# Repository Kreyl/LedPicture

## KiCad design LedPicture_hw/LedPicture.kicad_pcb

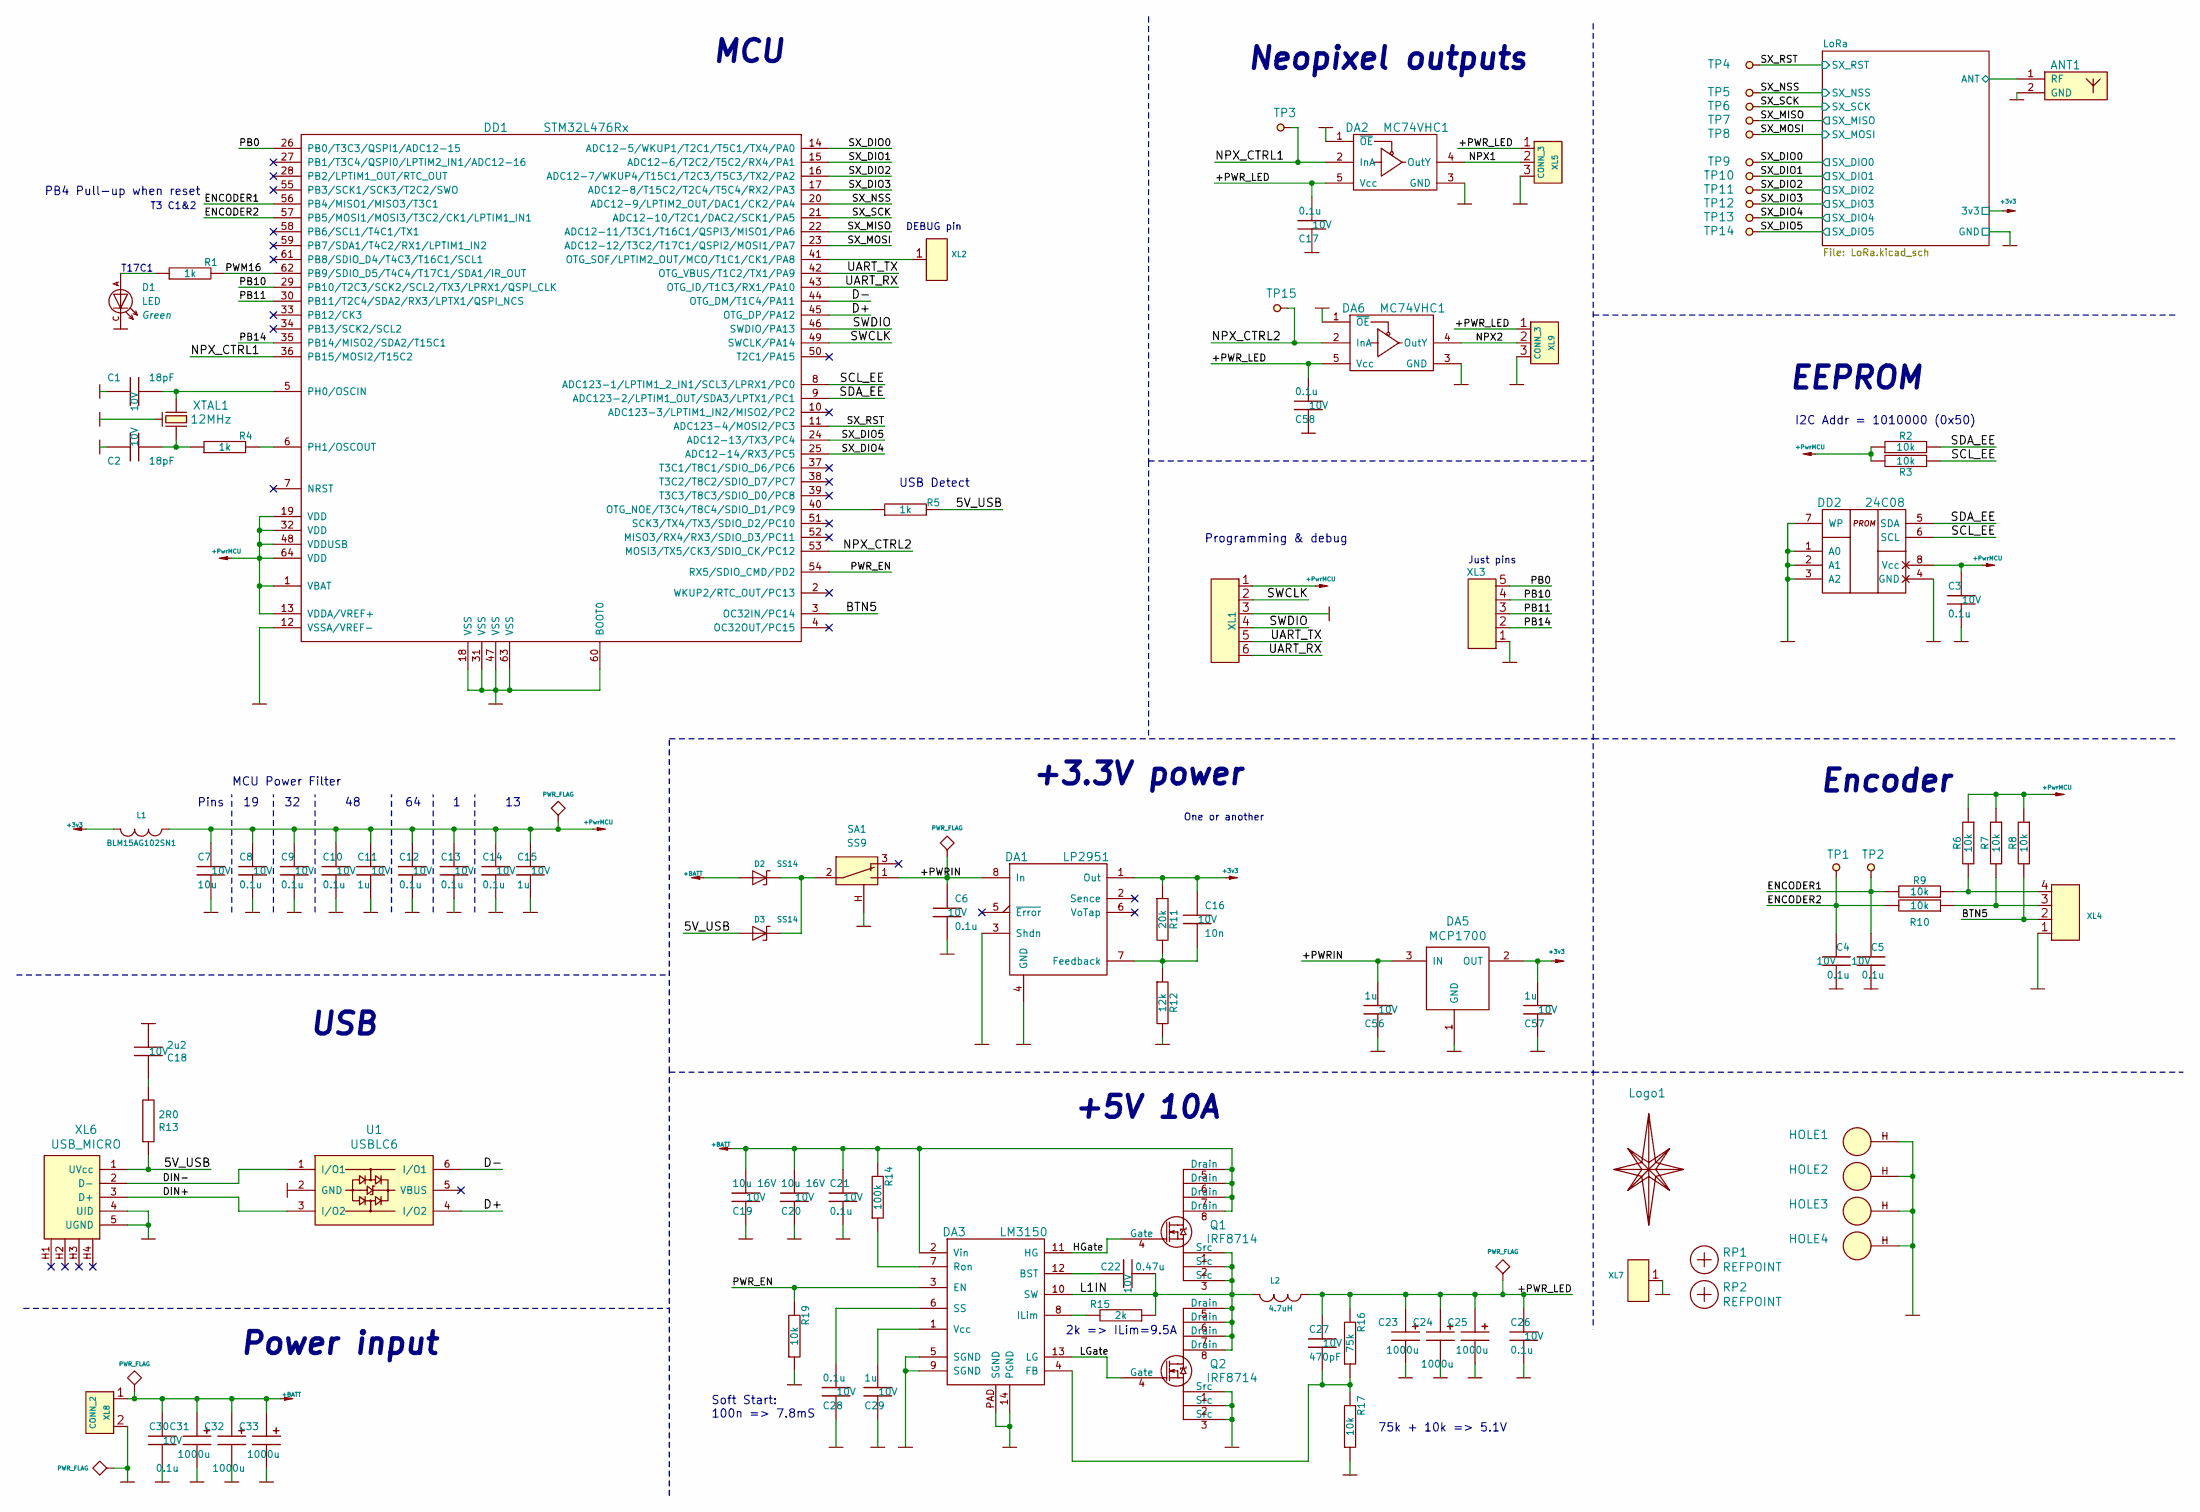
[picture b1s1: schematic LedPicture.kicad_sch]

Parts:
ANT1: ANT_GENERAL; ANT_868_IFA_SIMPLEJOY
C1, C2: 18pF; CAP_0603_Silks; Tolerance 20%; Voltage 10V
C3, C4, C5, C6, C8, C9, C10, C12, C13, C14, C17, C21, C26, C28, C30, C58: 0.1u; CAP_0603_Silks; Tolerance 20%; Voltage 10V
C7: 10u; CAP_0603_Silks; Tolerance 20%; Voltage 10V
C11, C15, C29, C56, C57: 1u; CAP_0603_Silks; Tolerance 20%; Voltage 10V
C16: 10n; CAP_0603_Silks; Tolerance 20%; Voltage 10V
C18: 2u2; CAP_0603_Silks; Tolerance 20%; Voltage 10V
C19, C20: 10u 16V; CAP_0603_Silks; Tolerance 20%; Voltage 10V
C22: 0.47u; CAP_0603_Silks; Tolerance 20%; Voltage 10V
C23, C24, C25, C31, C32, C33: 1000u; CAP_10xxR
C27: 470pF; CAP_0603_Silks; Tolerance 20%; Voltage 10V
D1: LED; LED_0603
D2, D3: SS14; SMA_DO214AC
DA1: LP2951; SO8_150MIL
DA2, DA6: MC74VHC1; SOT23-5
DA3: LM3150; HTSSOP14
DA5: MCP1700; SOT23-3A
DD1: STM32L476Rx; LQFP64
DD2: 24C08; SO8_150MIL
HOLE1, HOLE2, HOLE3, HOLE4: HOLE_METALLED; Hole3_5_out6mm
L1: BLM15AG102SN1; IND_0402; Tolerance 20%
L2: 4.7uH; 13x13
Logo1: Logo; Ostranna_16d9_13d5
Q1, Q2: IRF8714; SO8_150MIL
R1, R4, R5: 1k; RES_0603; Tolerance 1%
R2, R3, R6, R7, R8, R9, R10, R17, R19: 10k; RES_0603; Tolerance 1%
R11: 20k; RES_0603; Tolerance 1%
R12: 12k; RES_0603; Tolerance 1%
R13: 2R0; RES_0603; Tolerance 1%
R14: 100k; RES_0603; Tolerance 1%
R15: 2k; RES_0603; Tolerance 1%
R16: 75k; RES_0603; Tolerance 1%
RP1, RP2: REFPOINT; REF_POINT_1MM
SA1: SS9; SW_SS9
TP1, TP2, TP3, TP4, TP5, TP6, TP7, TP8, TP9, TP10, TP11, TP12, TP13, TP14, TP15: TESTPOINT; TESTPOINT_1MM
U1: USBLC6; SOT23-6
XL1: CONN_6; PLS-6_LOCK
XL2, XL7: CONN_1; PLS-1Rnd
XL3: CONN_5; PLS-5
XL4: CONN_4; WB-04(MW-4M)
XL5, XL9: CONN_3; TermiBlockHeader_508_x3_R
XL6: USB_MICRO; USBmicro_MOLEX_1050170001
XL8: CONN_2; TermiBlockHeader_508_x2_R
XTAL1: 12MHz; 03225C4

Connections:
+3v3: C16.1, C57.1, DA1.1 (Out), DA5.2 (OUT), L1.2, R11.1; also elsewhere on the board
+BATT: C19.1, C20.1, C21.2, C30.2, C31.1, C32.1, C33.1, D2.A, DA3.2 (Vin), Q1.5 (Drain), Q1.6 (Drain), Q1.7 (Drain), Q1.8 (Drain), R14.2, XL8.1
/5V_USB: D3.A, R5.2, R13.1, XL6.1 (UVcc)
/+PWRIN: C6.1, C56.1, DA1.8 (In), DA5.3 (IN), SA1.1
/+PWR_LED: C17.1, C23.1, C24.1, C25.1, C26.2, C27.2, C58.1, DA2.5 (Vcc), DA6.5 (Vcc), L2.1, R16.2, XL5.1, XL9.1
/BTN5: DD1.3 (OC32IN/PC14), R8.2, XL4.2 (PM)
/D+: DD1.45 (OTG_DP/PA12), U1.4 (I/O2)
/D-: DD1.44 (OTG_DM/T1C4/PA11), U1.6 (I/O1)
/DIN+: U1.3 (I/O2), XL6.3 (D+)
/DIN-: U1.1 (I/O1), XL6.2 (D-)
/ENCODER1: C5.2, DD1.56 (PB4/MISO1/MISO3/T3C1), R9.2, TP2.1
/ENCODER2: C4.2, DD1.57 (PB5/MOSI1/MOSI3/T3C2/CK1/LPTIM1_IN1), R10.2, TP1.1
/HGate: DA3.11 (HG), Q1.4 (Gate)
/L1IN: C22.1, DA3.10 (SW), L2.2, Q1.1 (Src), Q1.2 (Src), Q1.3 (Src), Q2.5 (Drain), Q2.6 (Drain), Q2.7 (Drain), Q2.8 (Drain), R15.1
/LGate: DA3.13 (LG), Q2.4 (Gate)
/LoRa/ANT: ANT1.1 (RF); also elsewhere on the board
/NPX1: DA2.4 (OutY), XL5.2 (PM)
/NPX2: DA6.4 (OutY), XL9.2 (PM)
/NPX_CTRL1: DA2.2 (InA), DD1.36 (PB15/MOSI2/T15C2), TP3.1
/NPX_CTRL2: DA6.2 (InA), DD1.53 (MOSI3/TX5/CK3/SDIO_CK/PC12), TP15.1
/PB0: DD1.26 (PB0/T3C3/QSPI1/ADC12-15), XL3.5
/PB10: DD1.29 (PB10/T2C3/SCK2/SCL2/TX3/LPRX1/QSPI_CLK), XL3.4
/PB11: DD1.30 (PB11/T2C4/SDA2/RX3/LPTX1/QSPI_NCS), XL3.3
/PB14: DD1.35 (PB14/MISO2/SDA2/T15C1), XL3.2
/PWM16: DD1.62 (PB9/SDIO_D5/T4C4/T17C1/SDA1/IR_OUT), R1.2
/PWR_EN: DA3.3 (EN), DD1.54 (RX5/SDIO_CMD/PD2), R19.2
/SCL_EE: DD1.8 (ADC123-1/LPTIM1_2_IN1/SCL3/LPRX1/PC0), DD2.6 (SCL), R3.1
/SDA_EE: DD1.9 (ADC123-2/LPTIM1_OUT/SDA3/LPTX1/PC1), DD2.5 (SDA), R2.2
/SWCLK: DD1.49 (SWCLK/PA14), XL1.2
/SWDIO: DD1.46 (SWDIO/PA13), XL1.4
/SX_DIO0: DD1.14 (ADC12-5/WKUP1/T2C1/T5C1/TX4/PA0), TP9.1; also elsewhere on the board
/SX_DIO1: DD1.15 (ADC12-6/T2C2/T5C2/RX4/PA1), TP10.1; also elsewhere on the board
/SX_DIO2: DD1.16 (ADC12-7/WKUP4/T15C1/T2C3/T5C3/TX2/PA2), TP11.1; also elsewhere on the board
/SX_DIO3: DD1.17 (ADC12-8/T15C2/T2C4/T5C4/RX2/PA3), TP12.1; also elsewhere on the board
/SX_DIO4: DD1.25 (ADC12-14/RX3/PC5), TP13.1; also elsewhere on the board
/SX_DIO5: DD1.24 (ADC12-13/TX3/PC4), TP14.1; also elsewhere on the board
/SX_MISO: DD1.22 (ADC12-11/T3C1/T16C1/QSPI3/MISO1/PA6), TP7.1; also elsewhere on the board
/SX_MOSI: DD1.23 (ADC12-12/T3C2/T17C1/QSPI2/MOSI1/PA7), TP8.1; also elsewhere on the board
/SX_NSS: DD1.20 (ADC12-9/LPTIM2_OUT/DAC1/CK2/PA4), TP5.1; also elsewhere on the board
/SX_RST: DD1.11 (ADC123-4/MOSI2/PC3), TP4.1; also elsewhere on the board
/SX_SCK: DD1.21 (ADC12-10/T2C1/DAC2/SCK1/PA5), TP6.1; also elsewhere on the board
/UART_RX: DD1.43 (OTG_ID/T1C3/RX1/PA10), XL1.6
/UART_TX: DD1.42 (OTG_VBUS/T1C2/TX1/PA9), XL1.5
GND: ANT1.2 (GND), C1.2, C2.2, C3.1, C4.1, C5.1, C6.2, C7.1, C8.1, C9.1, C10.1, C11.1, C12.1, C13.1, C14.1, C15.1, C17.2, C18.2, C19.2, C20.2, C21.1, C23.2, C24.2, C25.2, C26.1, C28.2, C29.2, C30.1, C31.2, C32.2, C33.2, C56.2, C57.2, C58.2, D1.C, DA1.3 (Shdn), DA1.4 (GND), DA2.1 (~OE), DA2.3 (GND), DA3.5 (SGND), DA3.9 (SGND), DA3.14 (PGND), DA3.PAD (SGND), DA5.1 (GND), DA6.1 (~OE), DA6.3 (GND), DD1.12 (VSSA/VREF-), DD1.18 (VSS), DD1.31 (VSS), DD1.47 (VSS), DD1.60 (BOOT0), DD1.63 (VSS), DD2.1 (A0), DD2.2 (A1), DD2.3 (A2), DD2.4 (GND), DD2.7 (WP), HOLE1.H, HOLE2.H, HOLE3.H, HOLE4.H, Q2.1 (Src), Q2.2 (Src), Q2.3 (Src), R12.2, R17.1, R19.1, SA1.H, U1.2 (GND), XL1.3, XL3.1, XL4.1, XL5.3, XL6.4 (UID), XL6.5 (UGND), XL7.1, XL8.2 (PM), XL9.3, XTAL1.H; also elsewhere on the board
unnamed: C1.1, DD1.5 (PH0/OSCIN), XTAL1.1
unnamed: C2.1, R4.1, XTAL1.2
unnamed: C16.2, DA1.7 (Feedback), R11.2, R12.1
unnamed: C18.1, R13.2
unnamed: C22.2, DA3.12 (BST)
unnamed: C27.1, DA3.4 (FB), R16.1, R17.2
unnamed: C28.1, DA3.6 (SS)
unnamed: C29.1, DA3.1 (Vcc)
unnamed: D1.A, R1.1
unnamed: D2.C, D3.C, SA1.2
unnamed: DA3.7 (Ron), R14.1
unnamed: DA3.8 (ILim), R15.2
unnamed: DD1.6 (PH1/OSCOUT), R4.2
unnamed: DD1.40 (OTG_NOE/T3C4/T8C4/SDIO_D1/PC9), R5.1
unnamed: DD1.41 (OTG_SOF/LPTIM2_OUT/MCO/T1C1/CK1/PA8), XL2.1
unnamed: R6.2, R9.1, XL4.4
unnamed: R7.2, R10.1, XL4.3

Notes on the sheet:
PB4 Pull-up when reset
T17C1
T3 C1&2
Pins 19 32 48 64 1 13
MCU Power Filter
Power input
USB
MCU
Soft Start: 100n => 7.8mS
USB Detect
DEBUG pin
+3.3V power
2k => ILim=9.5A
+5V 10A
One or another
Programming & debug
Neopixel outputs
75k + 10k => 5.1V
Just pins
EEPROM
I2C Addr = 1010000 (0x50)
Encoder

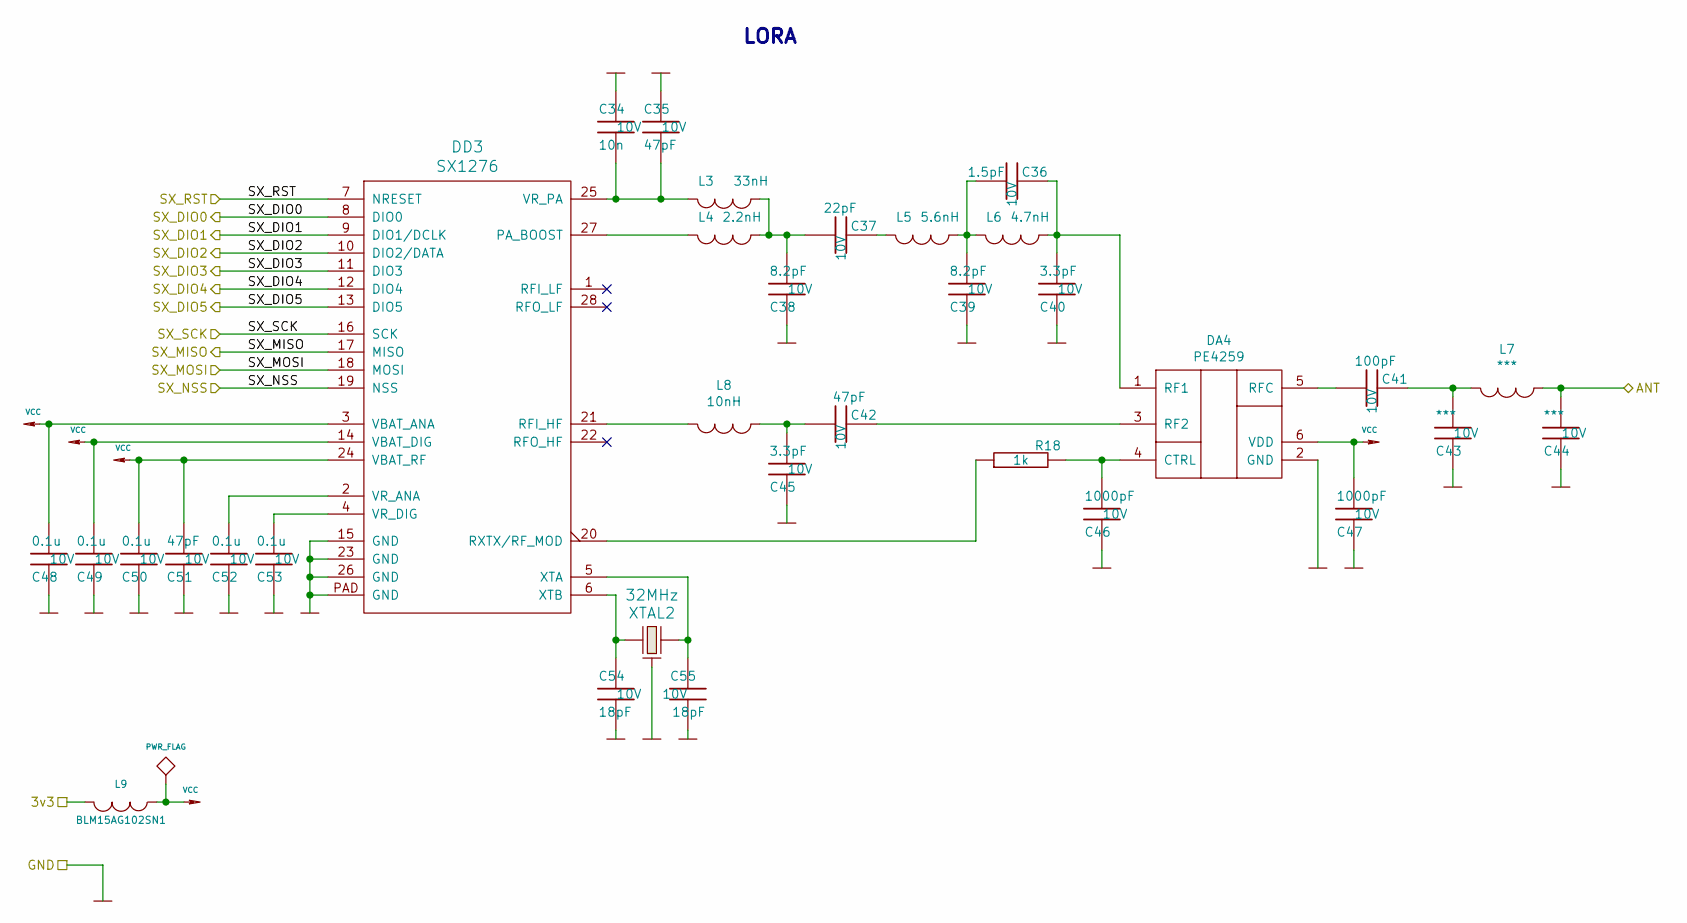
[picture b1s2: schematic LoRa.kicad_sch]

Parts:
C34: 10n; CAP_0402; Tolerance 20%; Voltage 10V
C35, C42, C51: 47pF; CAP_0402; Tolerance 20%; Voltage 10V
C36: 1.5pF; CAP_0402; Tolerance 20%; Voltage 10V
C37: 22pF; CAP_0402; Tolerance 20%; Voltage 10V
C38, C39: 8.2pF; CAP_0402; Tolerance 20%; Voltage 10V
C40, C45: 3.3pF; CAP_0402; Tolerance 20%; Voltage 10V
C41: 100pF; CAP_0402; Tolerance 20%; Voltage 10V
C43, C44: ***; CAP_0402; Tolerance 20%; Voltage 10V
C46, C47: 1000pF; CAP_0402; Tolerance 20%; Voltage 10V
C48, C49, C50, C52, C53: 0.1u; CAP_0402; Tolerance 20%; Voltage 10V
C54, C55: 18pF; CAP_0603_Silks; Tolerance 20%; Voltage 10V
DA4: PE4259; SC70
DD3: SX1276; QFN-28_EP_6x6_Pitch0.65mm
L3: 33nH; IND_0402; Tolerance 20%
L4: 2.2nH; IND_0402; Tolerance 20%
L5: 5.6nH; IND_0402; Tolerance 20%
L6: 4.7nH; IND_0402; Tolerance 20%
L7: ***; IND_0402; Tolerance 20%
L8: 10nH; IND_0402; Tolerance 20%
L9: BLM15AG102SN1; IND_0402; Tolerance 20%
R18: 1k; RES_0603; Tolerance 1%
XTAL2: 32MHz; 03225C4

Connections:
+3v3: L9.2; also elsewhere on the board
/LoRa/ANT: C44.1, L7.2; also elsewhere on the board
/SX_DIO0: DD3.8 (DIO0); also elsewhere on the board
/SX_DIO1: DD3.9 (DIO1/DCLK); also elsewhere on the board
/SX_DIO2: DD3.10 (DIO2/DATA); also elsewhere on the board
/SX_DIO3: DD3.11 (DIO3); also elsewhere on the board
/SX_DIO4: DD3.12 (DIO4); also elsewhere on the board
/SX_DIO5: DD3.13 (DIO5); also elsewhere on the board
/SX_MISO: DD3.17 (MISO); also elsewhere on the board
/SX_MOSI: DD3.18 (MOSI); also elsewhere on the board
/SX_NSS: DD3.19 (NSS); also elsewhere on the board
/SX_RST: DD3.7 (NRESET); also elsewhere on the board
/SX_SCK: DD3.16 (SCK); also elsewhere on the board
GND: C34.2, C35.2, C38.2, C39.2, C40.2, C43.2, C44.2, C45.2, C46.2, C47.2, C48.2, C49.2, C50.2, C51.2, C52.2, C53.2, C54.2, C55.2, DA4.2 (GND), DD3.15 (GND), DD3.23 (GND), DD3.26 (GND), DD3.PAD (GND), XTAL2.H; also elsewhere on the board
unnamed: C34.1, C35.1, DD3.25 (VR_PA), L3.1
unnamed: C36.1, C40.1, DA4.1 (RF1), L6.2
unnamed: C36.2, C39.1, L5.2, L6.1
unnamed: C37.1, L5.1
unnamed: C37.2, C38.1, L3.2, L4.2
unnamed: C41.1, C43.1, L7.1
unnamed: C41.2, DA4.5 (RFC)
unnamed: C42.1, DA4.3 (RF2)
unnamed: C42.2, C45.1, L8.2
unnamed: C46.1, DA4.4 (CTRL), R18.2
unnamed: C52.1, DD3.2 (VR_ANA)
unnamed: C53.1, DD3.4 (VR_DIG)
unnamed: C54.1, DD3.6 (XTB), XTAL2.2
unnamed: C55.1, DD3.5 (XTA), XTAL2.1
unnamed: DD3.20 (RXTX/RF_MOD), R18.1
unnamed: DD3.21 (RFI_HF), L8.1
unnamed: DD3.27 (PA_BOOST), L4.1
VCC: C47.1, C48.1, C49.1, C50.1, C51.1, DA4.6 (VDD), DD3.3 (VBAT_ANA), DD3.14 (VBAT_DIG), DD3.24 (VBAT_RF), L9.1

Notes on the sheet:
LORA

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
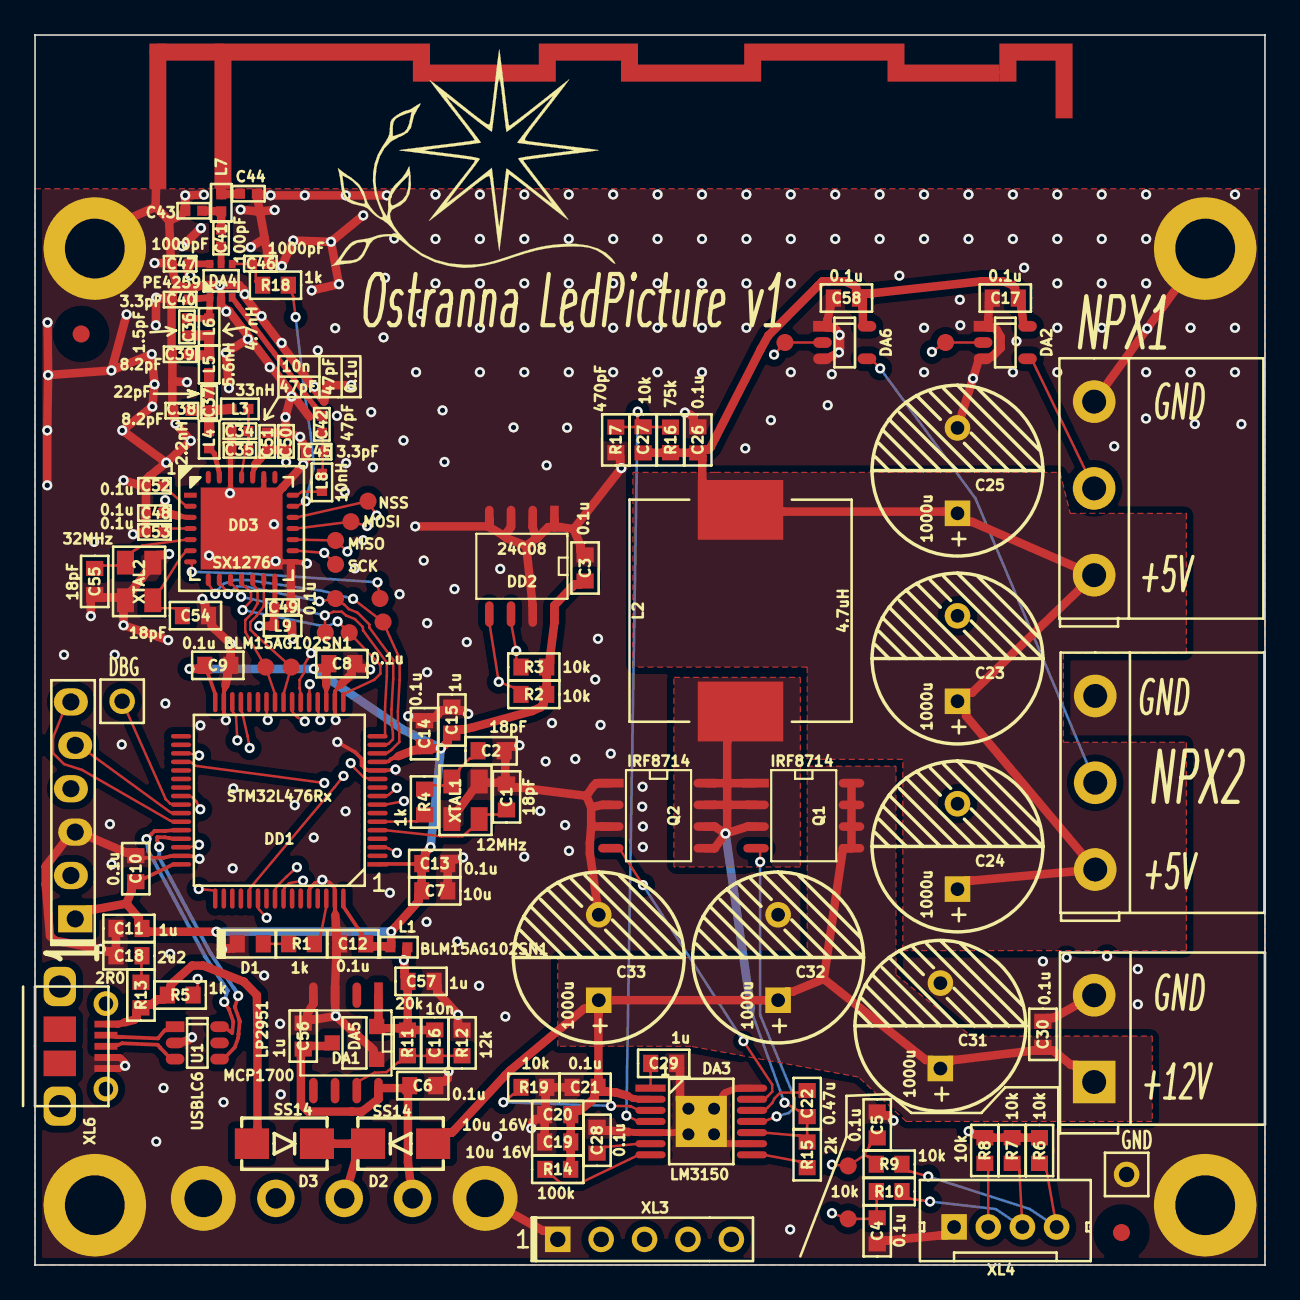
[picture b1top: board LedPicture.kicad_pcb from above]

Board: 4 copper layers, 72.0 x 72.0 mm, 136 parts (1 on the bottom side), 80 nets.
